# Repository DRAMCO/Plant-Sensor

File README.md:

# Plant Sensor
Documentation about the wireless plant sensing module.

# Photos

# Publications

## IEEE Sensors 2024 - Lightweight Energy-Constraint Wireless Sensor Solution for Plant Monitoring

### How to cite
```latex
@INPROCEEDINGS{10784661,
  author={Goossens, Sarah and Cappelle, Jona and Leenders, Guus and Reher, Thomas and De Smedt, Valentijn and Van de Poel, Bram and De Strycker, Lieven and Van der Perre, Liesbet},
  booktitle={2024 IEEE SENSORS}, 
  title={Lightweight Energy-Constraint Wireless Sensor Solution for Plant Monitoring}, 
  year={2024},
  volume={},
  number={},
  pages={1-4},
  keywords={Wireless communication;Smart agriculture;Wireless sensor networks;Tracking;Crops;Real-time systems;Sensors;Biomedical monitoring;Monitoring;Stress;Smart farming;horticulture;motion detection;IMU;LoRa;Internet of Things},
  doi={10.1109/SENSORS60989.2024.10784661}}
```

## IEEE Sensors Journal - Plant-wearable Wireless Sensing Solution for Autonomous Monitoring

### How to cite
```latex
@ARTICLE{11351320,
  author={Goossens, Sarah and Cappelle, Jona and Leenders, Guus and Reher, Thomas and Smedt, Valentijn De and Poel, Bram Van De and Strycker, Lieven De and Perre, Liesbet Van Der},
  journal={IEEE Sensors Journal}, 
  title={Plant-wearable Wireless Sensing Solution for Autonomous Monitoring}, 
  year={2026},
  volume={},
  number={},
  pages={1-1},
  keywords={Sensors;Crops;Wireless communication;Monitoring;Biomedical monitoring;Wireless sensor networks;Intelligent sensors;Green products;Batteries;Stress;Inertial Measurement Unit (IMU);plant monitoring;Horticultural sensor;plant-wearable;early stress detection;wireless connectivity},
  doi={10.1109/JSEN.2026.3651894}}
```

## IEEE Sensors 2025 - RF-Powered Batteryless Plant Movement Sensor for Precision Agriculture

### How to cite
```latex
@INPROCEEDINGS{11330430,
  author={Cappelle, Jona and Van Mulders, Jarne and Goossens, Sarah and Reher, Thomas and Van der Perre, Liesbet and De Strycker, Lieven and Van de Poel, Bram and Callebaut, Gilles},
  booktitle={2025 IEEE SENSORS}, 
  title={RF-Powered Batteryless Plant Movement Sensor for Precision Agriculture}, 
  year={2025},
  volume={},
  number={},
  pages={1-4},
  keywords={Radio frequency;Precision agriculture;Smart agriculture;Measurement units;Plants (biology);Maintenance;Synchronization;Internet of Things;Monitoring;Stress;Smart agriculture;Energy harvesting;Internet of Things},
  doi={10.1109/SENSORS59705.2025.11330430}}

```

## EUCNC 2025 - Attributional Life-cycle Assessment of Wireless Plant Sensing Module
[Detailed description of the LCA](LCA/Detailed_impact.md)

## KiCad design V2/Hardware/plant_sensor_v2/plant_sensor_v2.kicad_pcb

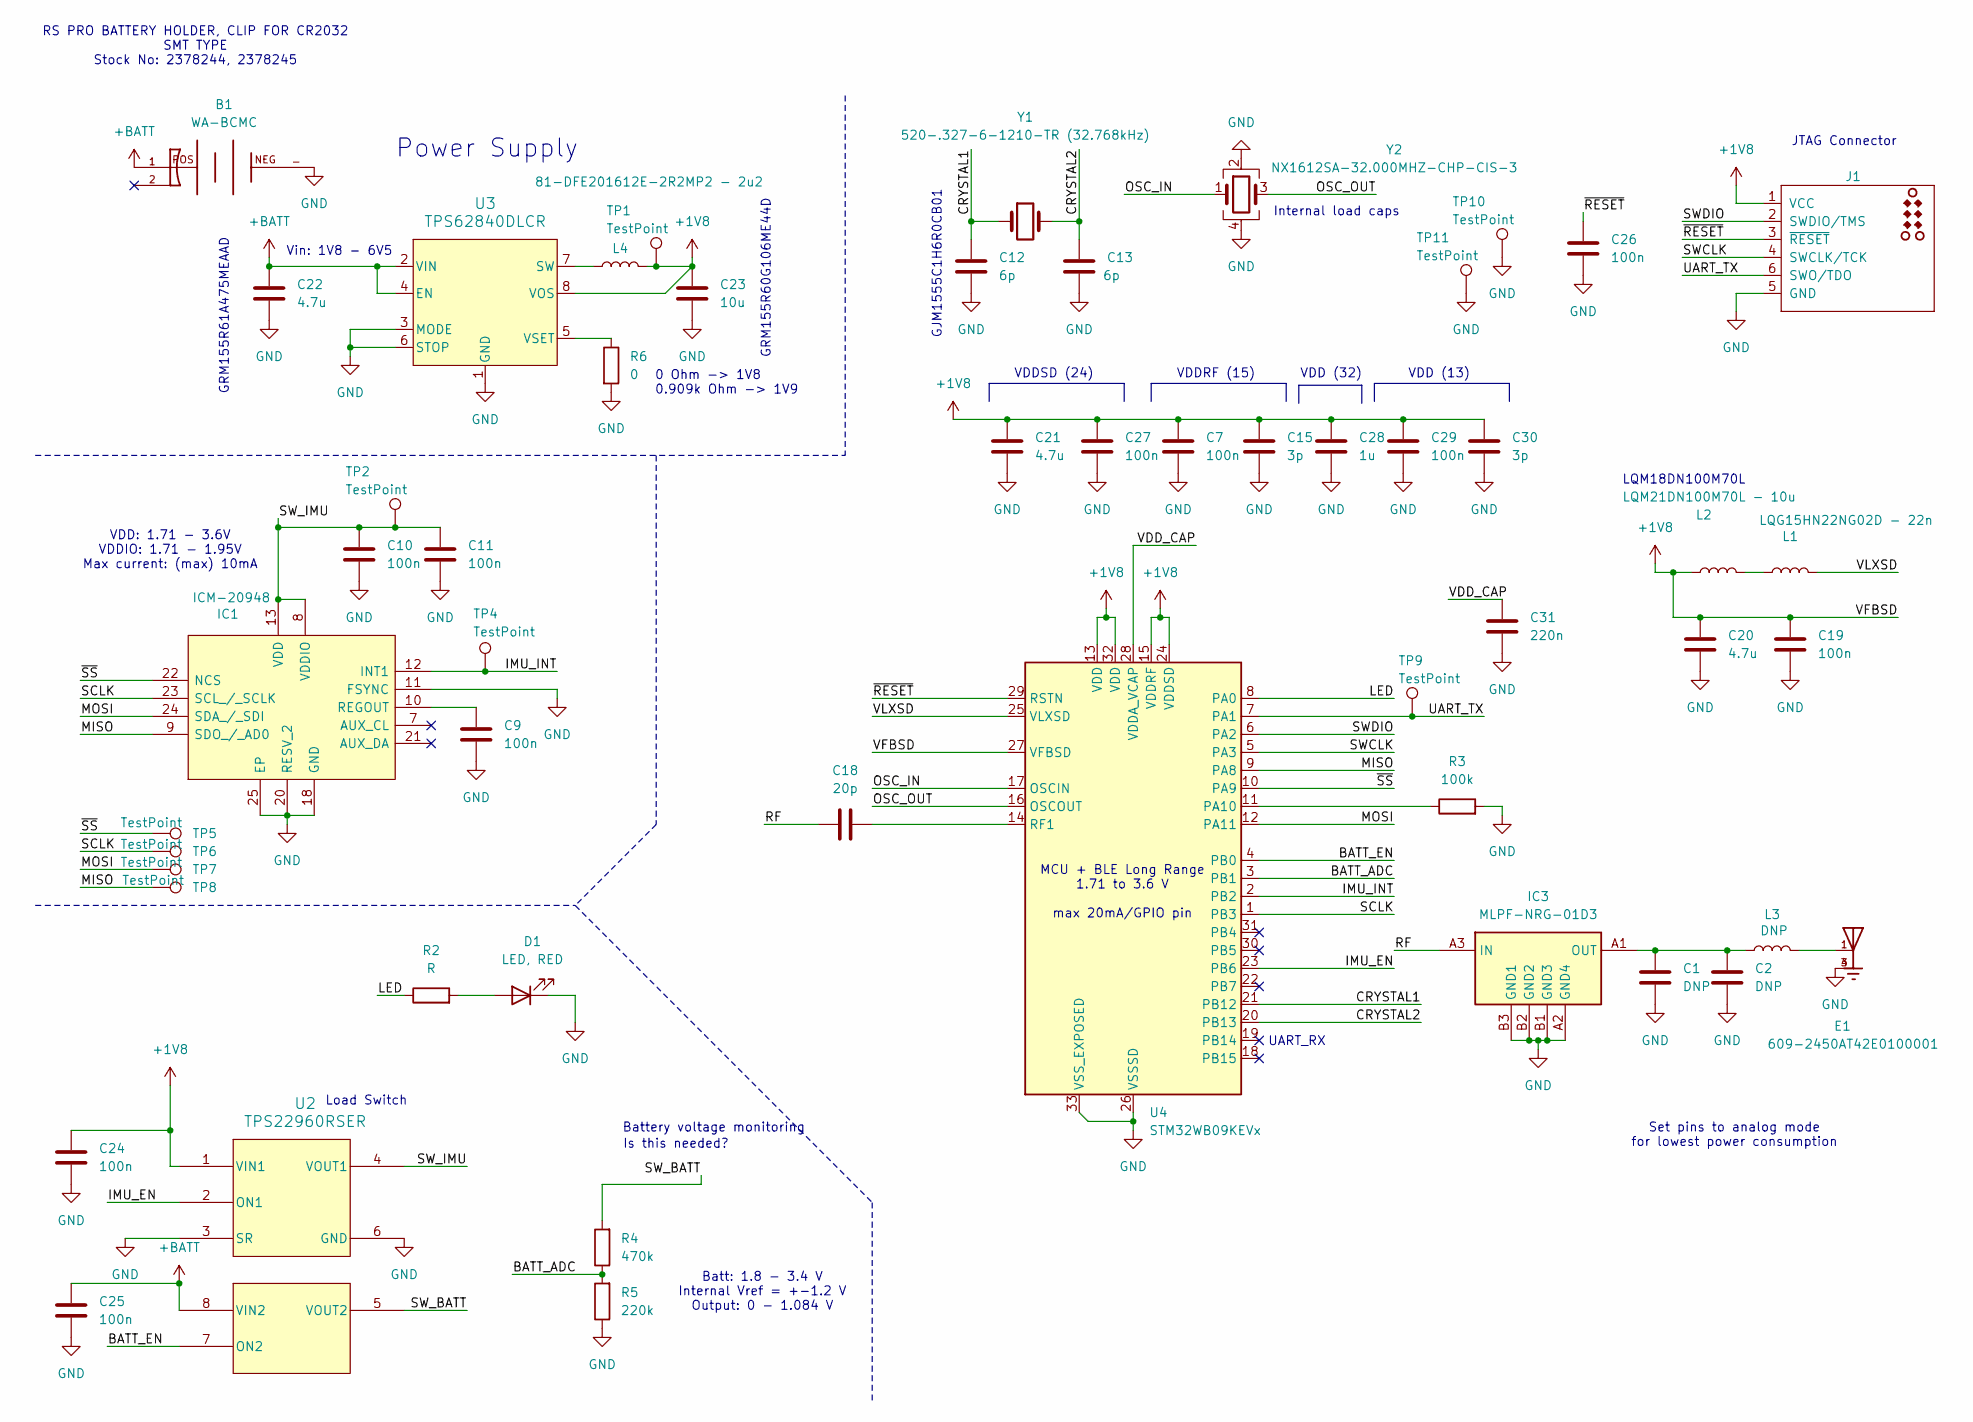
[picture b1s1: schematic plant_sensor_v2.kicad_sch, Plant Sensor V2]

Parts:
B1: WA-BCMC; WA-BCMC_79523211; PART-NUMBER 79523141
C1, C2: DNP; C_0402_1005Metric
C7, C9, C10, C11, C19, C24, C25, C26, C27, C29: 100n; C_0402_1005Metric
C12, C13: 6p; C_0402_1005Metric
C15, C30: 3p; C_0201_0603Metric
C18: 20p; C_0402_1005Metric
C20, C21, C22: 4.7u; C_0402_1005Metric
C23: 10u; C_0402_1005Metric
C28: 1u; C_0402_1005Metric
C31: 220n; C_0402_1005Metric
D1: LED, RED; LED_0603_1608Metric
E1: 609-2450AT42E0100001; XDCR_2450AT42E0100E; PARTREV 1.3
IC1: ICM-20948; ICM20948; Mouser Part Number 410-ICM-20948
IC3: MLPF-NRG-01D3; MLPFNRG01D3; Mouser Part Number 511-MLPF-NRG-01D3
J1: TC2030_SWD-MCP-NL; Tag-Connect_TC2030-IDC-NL_2x03_P1.27mm_Vertical
L1: LQG15HN22NG02D - 22n; L_0402_1005Metric
L2: LQM21DN100M70L - 10u; L_0805_2012Metric
L3: DNP; L_0402_1005Metric
L4: 81-DFE201612E-2R2MP2 - 2u2; L_Murata_DFE201610P
R2: R; R_0402_1005Metric
R3: 100k; R_0402_1005Metric
R4: 470k; R_0402_1005Metric
R5: 220k; R_0402_1005Metric
R6: 0; R_0402_1005Metric
TP1, TP2, TP4, TP5, TP6, TP7, TP8, TP9, TP10, TP11: TestPoint; TestPoint_Pad_D1.0mm
U2: TPS22960RSER; RSE0008A
U3: TPS62840DLCR; VSON8_2P1X1P6_TEX
U4: STM32WB09KEVx; QFN-32-1EP_5x5mm_P0.5mm_EP3.7x3.7mm
Y1: 520-.327-6-1210-TR (32.768kHz); XTAL_ECS-.327-6-1210-TR
Y2: NX1612SA-32.000MHZ-CHP-CIS-3; OSCSC105P160X120X35-4N

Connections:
+1V8: C7.1, C15.1, C19.1, C20.1, C21.1, C23.1, C24.1, C27.1, C28.1, C29.1, C30.1, J1.1 (VCC), L2.1, L4.2, TP1.1, U2.1 (VIN1), U3.8 (VOS), U4.13 (VDD), U4.15 (VDDRF), U4.24 (VDDSD), U4.27 (VFBSD), U4.32 (VDD)
+BATT: B1.1, C22.1, C25.1, U2.8 (VIN2), U3.2 (VIN), U3.4 (EN)
/BATT_ADC: R4.1, R5.2, U4.3 (PB1)
/BATT_EN: U2.7 (ON2), U4.4 (PB0)
/CRYSTAL1: C12.1, U4.21 (PB12), Y1.1
/CRYSTAL2: C13.1, U4.20 (PB13), Y1.2
/IMU_EN: U2.2 (ON1), U4.23 (PB6)
/IMU_INT: IC1.12 (INT1), TP4.1, U4.2 (PB2)
/LED: R2.1, U4.8 (PA0)
/MISO: IC1.9 (SDO_/_AD0), TP8.1, U4.9 (PA8)
/MOSI: IC1.24 (SDA_/_SDI), TP7.1, U4.12 (PA11)
/OSC_IN: U4.17 (OSCIN), Y2.1
/OSC_OUT: U4.16 (OSCOUT), Y2.3
/RF: C18.1, IC3.A3 (IN)
/SCLK: IC1.23 (SCL_/_SCLK), TP6.1, U4.1 (PB3)
/SWCLK: J1.4 (SWCLK/TCK), U4.5 (PA3)
/SWDIO: J1.2 (SWDIO/TMS), U4.6 (PA2)
/SW_BATT: R4.2, U2.5 (VOUT2)
/SW_IMU: C10.1, C11.1, IC1.8 (VDDIO), IC1.13 (VDD), TP2.1, U2.4 (VOUT1)
/UART_TX: J1.6 (SWO/TDO), TP9.1, U4.7 (PA1)
/VDD_CAP: C31.1, U4.28 (VDDA_VCAP)
/VLXSD: L1.2, U4.25 (VLXSD)
/~RESET: C26.2, J1.3 (~RESET), U4.29 (RSTN)
/~SS: IC1.22 (NCS), TP5.1, U4.10 (PA9)
GND: B1.-, C1.2, C2.2, C7.2, C9.2, C10.2, C11.2, C12.2, C13.2, C15.2, C19.2, C20.2, C21.2, C22.2, C23.2, C24.2, C25.2, C26.1, C27.2, C28.2, C29.2, C30.2, C31.2, D1.1 (K), E1.3, E1.4, IC1.11 (FSYNC), IC1.18 (GND), IC1.20 (RESV_2), IC1.25 (EP), IC3.A2 (GND4), IC3.B1 (GND3), IC3.B2 (GND2), IC3.B3 (GND1), J1.5 (GND), R3.2, R5.1, R6.2, TP10.1, TP11.1, U2.3 (SR), U2.6 (GND), U3.1 (GND), U3.3 (MODE), U3.6 (STOP), U4.26 (VSSSD), U4.33 (VSS_EXPOSED), Y2.2, Y2.4
unnamed: D1.2 (A), R2.2
unnamed: E1.1, L3.2
unnamed: C9.1, IC1.10 (REGOUT)
unnamed: C1.1, C2.1, IC3.A1 (OUT), L3.1
unnamed: L1.1, L2.2
unnamed: L4.1, U3.7 (SW)
unnamed: R6.1, U3.5 (VSET)
unnamed: R3.1, U4.11 (PA10)
unnamed: C18.2, U4.14 (RF1)

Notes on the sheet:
UART_RX
MCU + BLE Long Range 1.71 to 3.6 V max 20mA/GPIO pin
Vin: 1V8 - 6V5
Internal load caps
GRM155R60G106ME44D
Power Supply
RS PRO BATTERY HOLDER, CLIP FOR CR2032 SMT TYPE Stock No: 2378244, 2378245
GRM155R61A475MEAAD
VDD (32)
Battery voltage monitoring
JTAG Connector
Load Switch
Is this needed?
LQM18DN100M70L
Set pins to analog mode for lowest power consumption
VDD: 1.71 - 3.6V VDDIO: 1.71 - 1.95V Max current: (max) 10mA
VDD (13)
Batt: 1.8 - 3.4 V Internal Vref = +-1.2 V Output: 0 - 1.084 V
0 Ohm -> 1V8 0.909k Ohm -> 1V9
VDDSD (24)
VDDRF (15)
GJM1555C1H6R0CB01

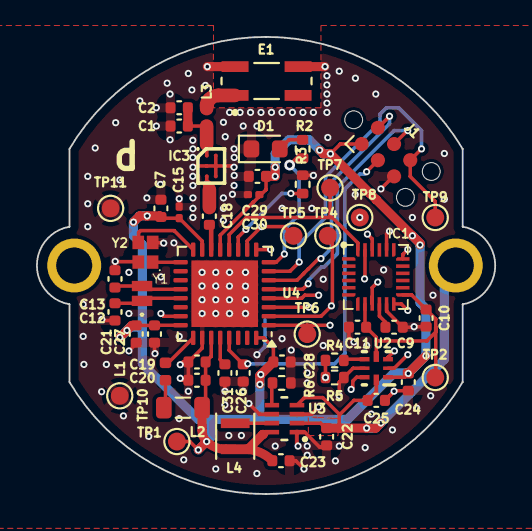
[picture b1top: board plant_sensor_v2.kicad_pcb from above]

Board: 4 copper layers, 25.5 x 25.4 mm, 53 parts (1 on the bottom side), 34 nets.

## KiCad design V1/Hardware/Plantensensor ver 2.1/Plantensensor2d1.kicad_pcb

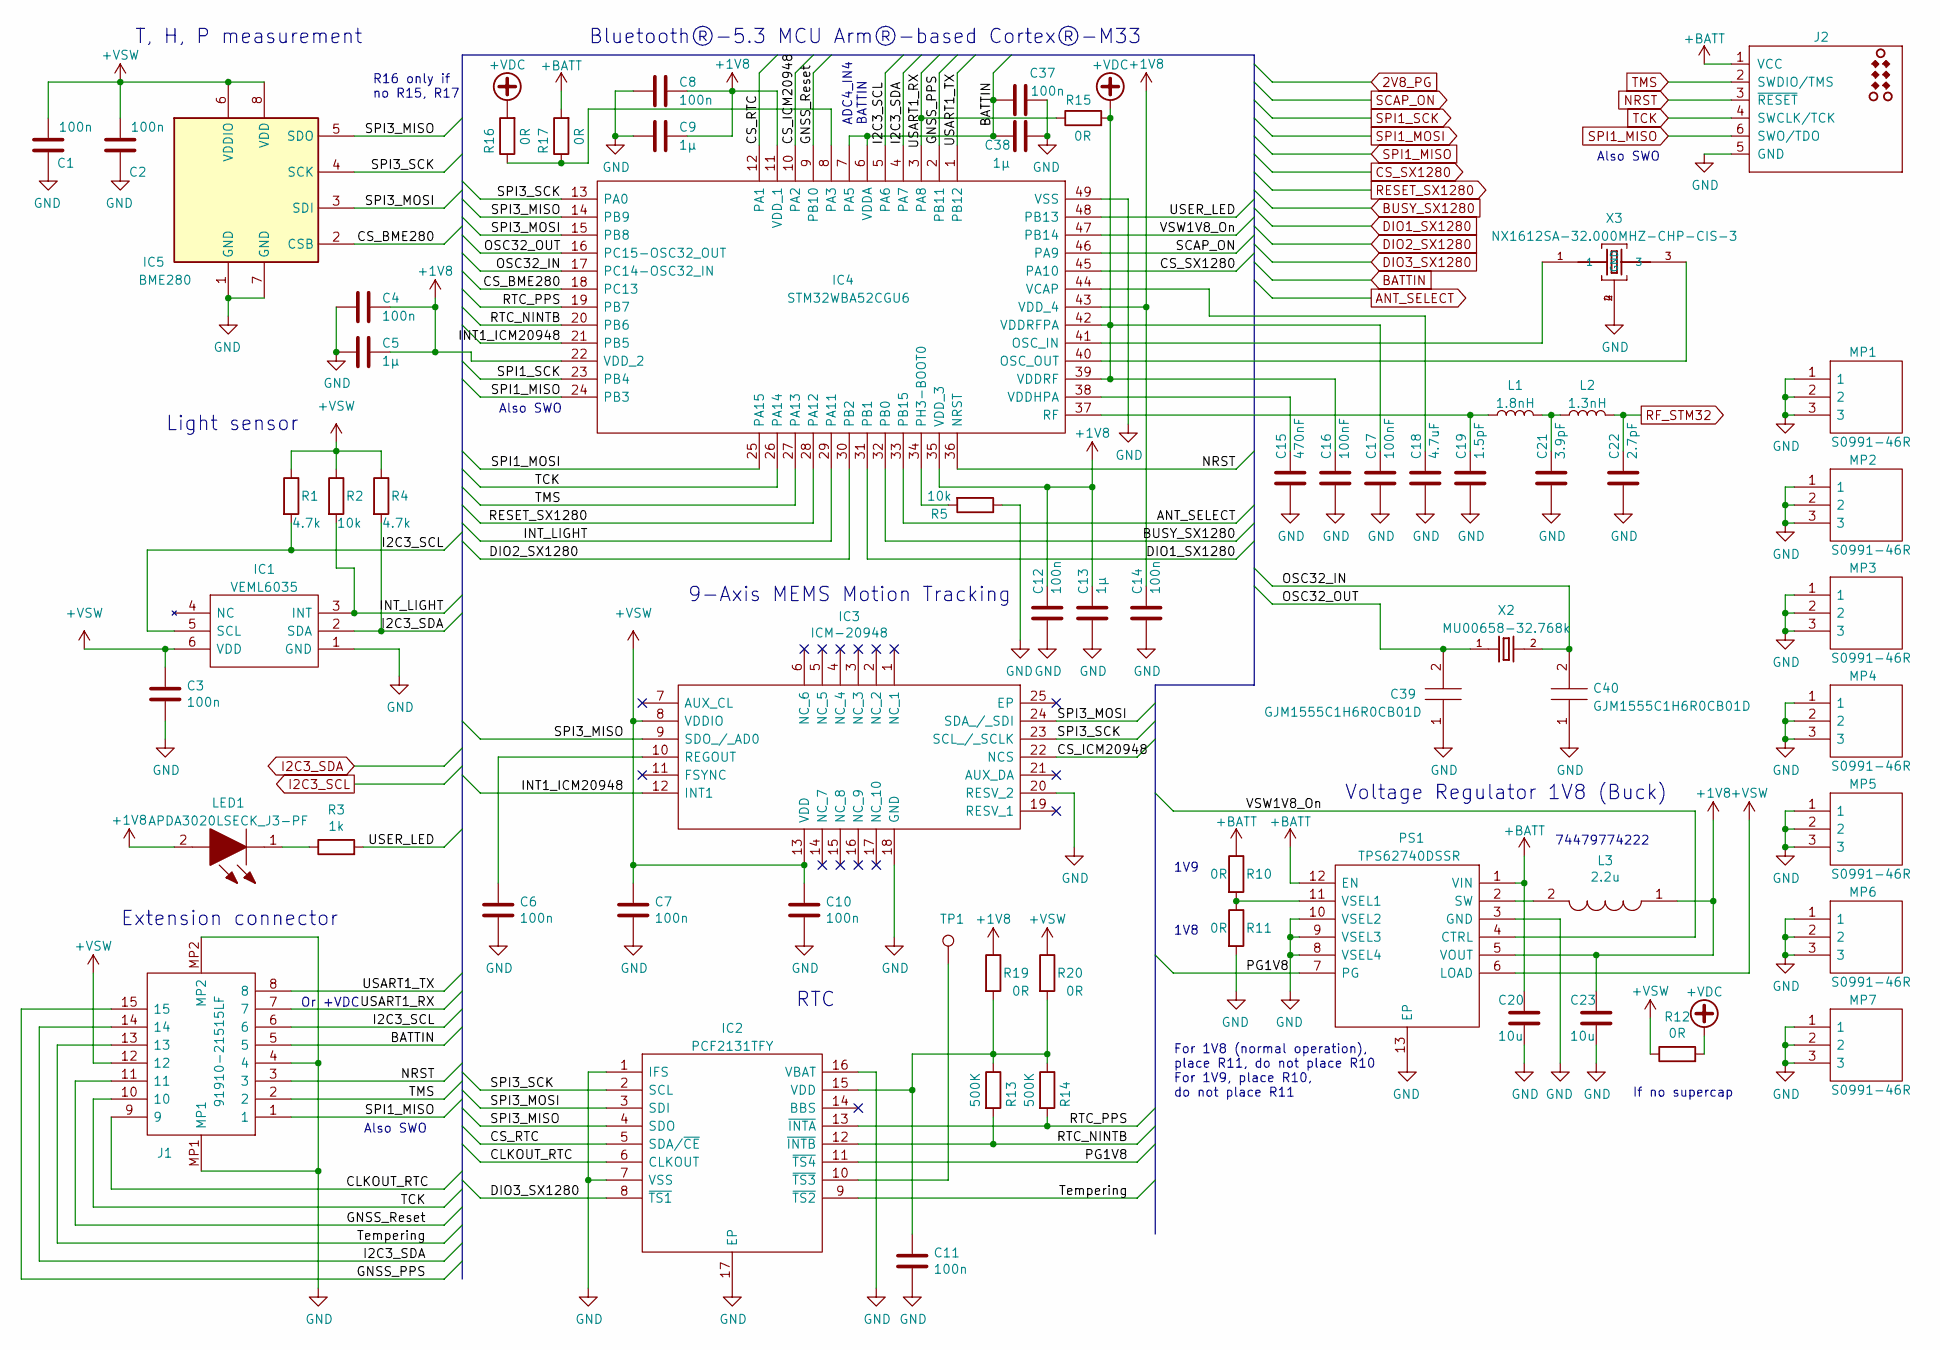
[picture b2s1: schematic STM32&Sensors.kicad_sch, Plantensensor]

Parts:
C1, C2, C3, C4, C6, C7, C8, C10, C11, C12, C14, C37: 100n; C_0402_1005Metric
C5, C9, C13, C38: 1µ; C_0603_1608Metric
C15: 470nF; C_0603_1608Metric
C16, C17: 100nF; C_0402_1005Metric
C18: 4.7uF; C_0805_2012Metric
C19: 1.5pF; C_0402_1005Metric
C20, C23: 10u; C_0805_2012Metric
C21: 3.9pF; C_0402_1005Metric
C22: 2.7pF; C_0402_1005Metric
C39, C40: GJM1555C1H6R0CB01D; CAPC1005X55N; Mouser Part Number 81-GJM1555C1H6R0CB01
IC1: VEML6035; Mouser Part Number 78-VEML6035
IC2: PCF2131TFY; SON50P350X450X150-17N-D_PCF2131TFY; Mouser Part Number 771-PCF2131TFY
IC3: ICM-20948; QFN40P300X300X105-25N-D_ICM20948; Mouser Part Number 410-ICM-20948
IC4: STM32WBA52CGU6; QFN50P700X700X65-49N-D; Mouser Part Number 511-STM32WBA52CGU6
IC5: BME280; Bosch_LGA-8_2.5x2.5mm_P0.65mm_ClockwisePinNumbering
J1: 91910-21515LF; 9191021515LF; Mouser Part Number 649-91910-21515LF
J2: TC2030_SWD-MCP-NL; TC2030-MCP-NL
L1: 1.8nH; C_0402_1005Metric
L2: 1.3nH; C_0402_1005Metric
L3: 2.2u; L_0805_2012Metric; Mouser Part Number 710-74479774222
LED1: APDA3020LSECK_J3-PF; APDA3020LSECKJ3PF; Mouser Part Number 604-APDA3020LSECKJ3F
MP1, MP2, MP3, MP4, MP5, MP6, MP7: S0991-46R; S099146R; Mouser Part Number 855-S0991-46R
PS1: TPS62740DSSR; SON50P200X300X80-13N_TPS62740DSSR; Mouser Part Number 595-TPS62740DSSR
R1, R4: 4.7k; R_0402_1005Metric
R2, R5: 10k; R_0402_1005Metric
R3: 1k; R_0603_1608Metric
R10, R11, R15, R16, R17, R19, R20: 0R; R_0402_1005Metric
R12: 0R; R_0603_1608Metric
R13, R14: 500K; R_0402_1005Metric
TP1: TestPoint; TestPoint_Pad_D1.0mm
X2: MU00658-32.768k; XTAL_ECS-.327-12.5-16-TR; DigiKey_Part_Number XC2131TR-ND
X3: NX1612SA-32.000MHZ-CHP-CIS-3; OSCSC105P160X120X35-4N

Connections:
+1V8: C4.1, C5.1, C8.1, C9.1, C12.1, C13.1, C14.1, C23.1, IC4.11 (VDD_1), IC4.22 (VDD_2), IC4.35 (VDD_3), IC4.43 (VDD_4), L3.1, LED1.2, PS1.5 (VOUT), R19.1
+BATT: C20.1, J2.1 (VCC), PS1.1 (VIN), PS1.12 (EN), R10.1, R17.2; also elsewhere on the board
+VDC: C16.1, C17.1, IC4.39 (VDDRF), IC4.42 (VDDRFPA), R12.2, R15.2, R16.2; also elsewhere on the board
+VSW: C1.1, C2.1, C3.1, C7.1, C10.1, IC1.6 (VDD), IC3.8 (VDDIO), IC3.13 (VDD), IC5.6 (VDDIO), IC5.8 (VDD), J1.12, PS1.6 (LOAD), R1.1, R2.1, R4.1, R12.1, R20.1; also elsewhere on the board
/STM32&Sensors/CLKOUT_RTC: IC2.6 (CLKOUT), J1.9
/STM32&Sensors/CS_BME280: IC4.18 (PC13), IC5.2 (CSB)
/STM32&Sensors/CS_ICM20948: IC3.22 (NCS), IC4.10 (PA2)
/STM32&Sensors/CS_RTC: IC2.5 (SDA/~CE), IC4.12 (PA1)
/STM32&Sensors/GNSS_PPS: IC4.2 (PB11), J1.15
/STM32&Sensors/GNSS_Reset: IC4.9 (PB10), J1.11
/STM32&Sensors/INT1_ICM20948: IC3.12 (INT1), IC4.21 (PB5)
/STM32&Sensors/INT_LIGHT: IC1.3 (INT), IC4.29 (PA11), R2.2
/STM32&Sensors/OSC32_IN: C40.2, IC4.17 (PC14-OSC32_IN), X2.2
/STM32&Sensors/OSC32_OUT: C39.2, IC4.16 (PC15-OSC32_OUT), X2.1
/STM32&Sensors/PG1V8: IC2.11 (~TS4), PS1.7 (PG)
/STM32&Sensors/RTC_NINTB: IC2.12 (~INTB), IC4.20 (PB6), R13.2
/STM32&Sensors/RTC_PPS: IC2.13 (~INTA), IC4.19 (PB7), R14.2
/STM32&Sensors/SPI3_MISO: IC2.4 (SDO), IC3.9 (SDO_/_AD0), IC4.14 (PB9), IC5.5 (SDO)
/STM32&Sensors/SPI3_MOSI: IC2.3 (SDI), IC3.24 (SDA_/_SDI), IC4.15 (PB8), IC5.3 (SDI)
/STM32&Sensors/SPI3_SCK: IC2.2 (SCL), IC3.23 (SCL_/_SCLK), IC4.13 (PA0), IC5.4 (SCK)
/STM32&Sensors/Tempering: IC2.9 (~TS2), J1.13
/STM32&Sensors/USART1_RX: IC4.3 (PA8), J1.7, R15.1
/STM32&Sensors/USART1_TX: IC4.1 (PB12), J1.8
/STM32&Sensors/USER_LED: IC4.48 (PB13), R3.2
/STM32&Sensors/VSW1V8_On: IC4.47 (PB14), PS1.4 (CTRL)
ANT_SELECT: IC4.33 (PB15); also elsewhere on the board
BATTIN: C37.1, C38.1, IC4.6 (VDDA), IC4.7 (PA5), J1.5; also elsewhere on the board
BUSY_SX1280: IC4.32 (PB0); also elsewhere on the board
CS_SX1280: IC4.45 (PA10); also elsewhere on the board
DIO1_SX1280: IC4.31 (PB1); also elsewhere on the board
DIO2_SX1280: IC4.30 (PB2); also elsewhere on the board
DIO3_SX1280: IC2.8 (~TS1); also elsewhere on the board
GND: C1.2, C2.2, C3.2, C4.2, C5.2, C6.2, C7.2, C8.2, C9.2, C10.2, C11.2, C12.2, C13.2, C14.2, C15.2, C16.2, C17.2, C18.2, C19.2, C20.2, C21.2, C22.2, C23.2, C37.2, C38.2, C39.1, C40.1, IC1.1 (GND), IC2.1 (IFS), IC2.7 (VSS), IC2.16 (VBAT), IC2.17 (EP), IC3.18 (GND), IC3.20 (RESV_2), IC4.49 (VSS), IC5.1 (GND), IC5.7 (GND), J1.4, J1.MP1, J1.MP2, J2.5 (GND), MP1.1, MP1.2, MP1.3, MP2.1, MP2.2, MP2.3, MP3.1, MP3.2, MP3.3, MP4.1, MP4.2, MP4.3, MP5.1, MP5.2, MP5.3, MP6.1, MP6.2, MP6.3, MP7.1, MP7.2, MP7.3, PS1.3 (GND), PS1.8 (VSEL4), PS1.9 (VSEL3), PS1.10 (VSEL2), PS1.13 (EP), R5.1, R11.2, X3.2 (GND), X3.4 (GND); also elsewhere on the board
I2C3_SCL: IC1.5 (SCL), IC4.5 (PA6), J1.6, R1.2; also elsewhere on the board
I2C3_SDA: IC1.2 (SDA), IC4.4 (PA7), J1.14, R4.2; also elsewhere on the board
NRST: IC4.36 (NRST), J1.3, J2.3 (~RESET)
unnamed: C6.1, IC3.10 (REGOUT)
unnamed: C11.1, IC2.15 (VDD), R13.1, R14.1, R19.2, R20.2
unnamed: C15.1, IC4.38 (VDDHPA)
unnamed: C18.1, IC4.44 (VCAP)
unnamed: C19.1, IC4.37 (RF), L1.1
unnamed: C21.1, L1.2, L2.1
unnamed: IC2.10 (~TS3), TP1.1
unnamed: IC4.8 (PA3), R16.1, R17.1
unnamed: IC4.34 (PH3-BOOT0), R5.2
unnamed: IC4.40 (OSC_OUT), X3.3
unnamed: IC4.41 (OSC_IN), X3.1
unnamed: L3.2, PS1.2 (SW)
unnamed: LED1.1, R3.1
unnamed: PS1.11 (VSEL1), R10.2, R11.1
RESET_SX1280: IC4.28 (PA12); also elsewhere on the board
RF_STM32: C22.1, L2.2; also elsewhere on the board
SCAP_ON: IC4.46 (PA9); also elsewhere on the board
SPI1_MISO: IC4.24 (PB3), J1.1, J2.6 (SWO/TDO); also elsewhere on the board
SPI1_MOSI: IC4.25 (PA15); also elsewhere on the board
SPI1_SCK: IC4.23 (PB4); also elsewhere on the board
TCK: IC4.26 (PA14), J1.10, J2.4 (SWCLK/TCK)
TMS: IC4.27 (PA13), J1.2, J2.2 (SWDIO/TMS)

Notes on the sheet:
Voltage Regulator 1V8 (Buck)
R16 only if no R15, R17
9-Axis MEMS Motion Tracking
Extension connector
RTC
ADC4_IN4 BATTIN
Also SWO
Light sensor
1V8
Bluetooth®-5.3 MCU Arm®-based Cortex®-M33
74479774222
Or +VDC
For 1V8 (normal operation), place R11, do not place R10 For 1V9, place R10, do not place R11
T, H, P measurement
If no supercap
1V9

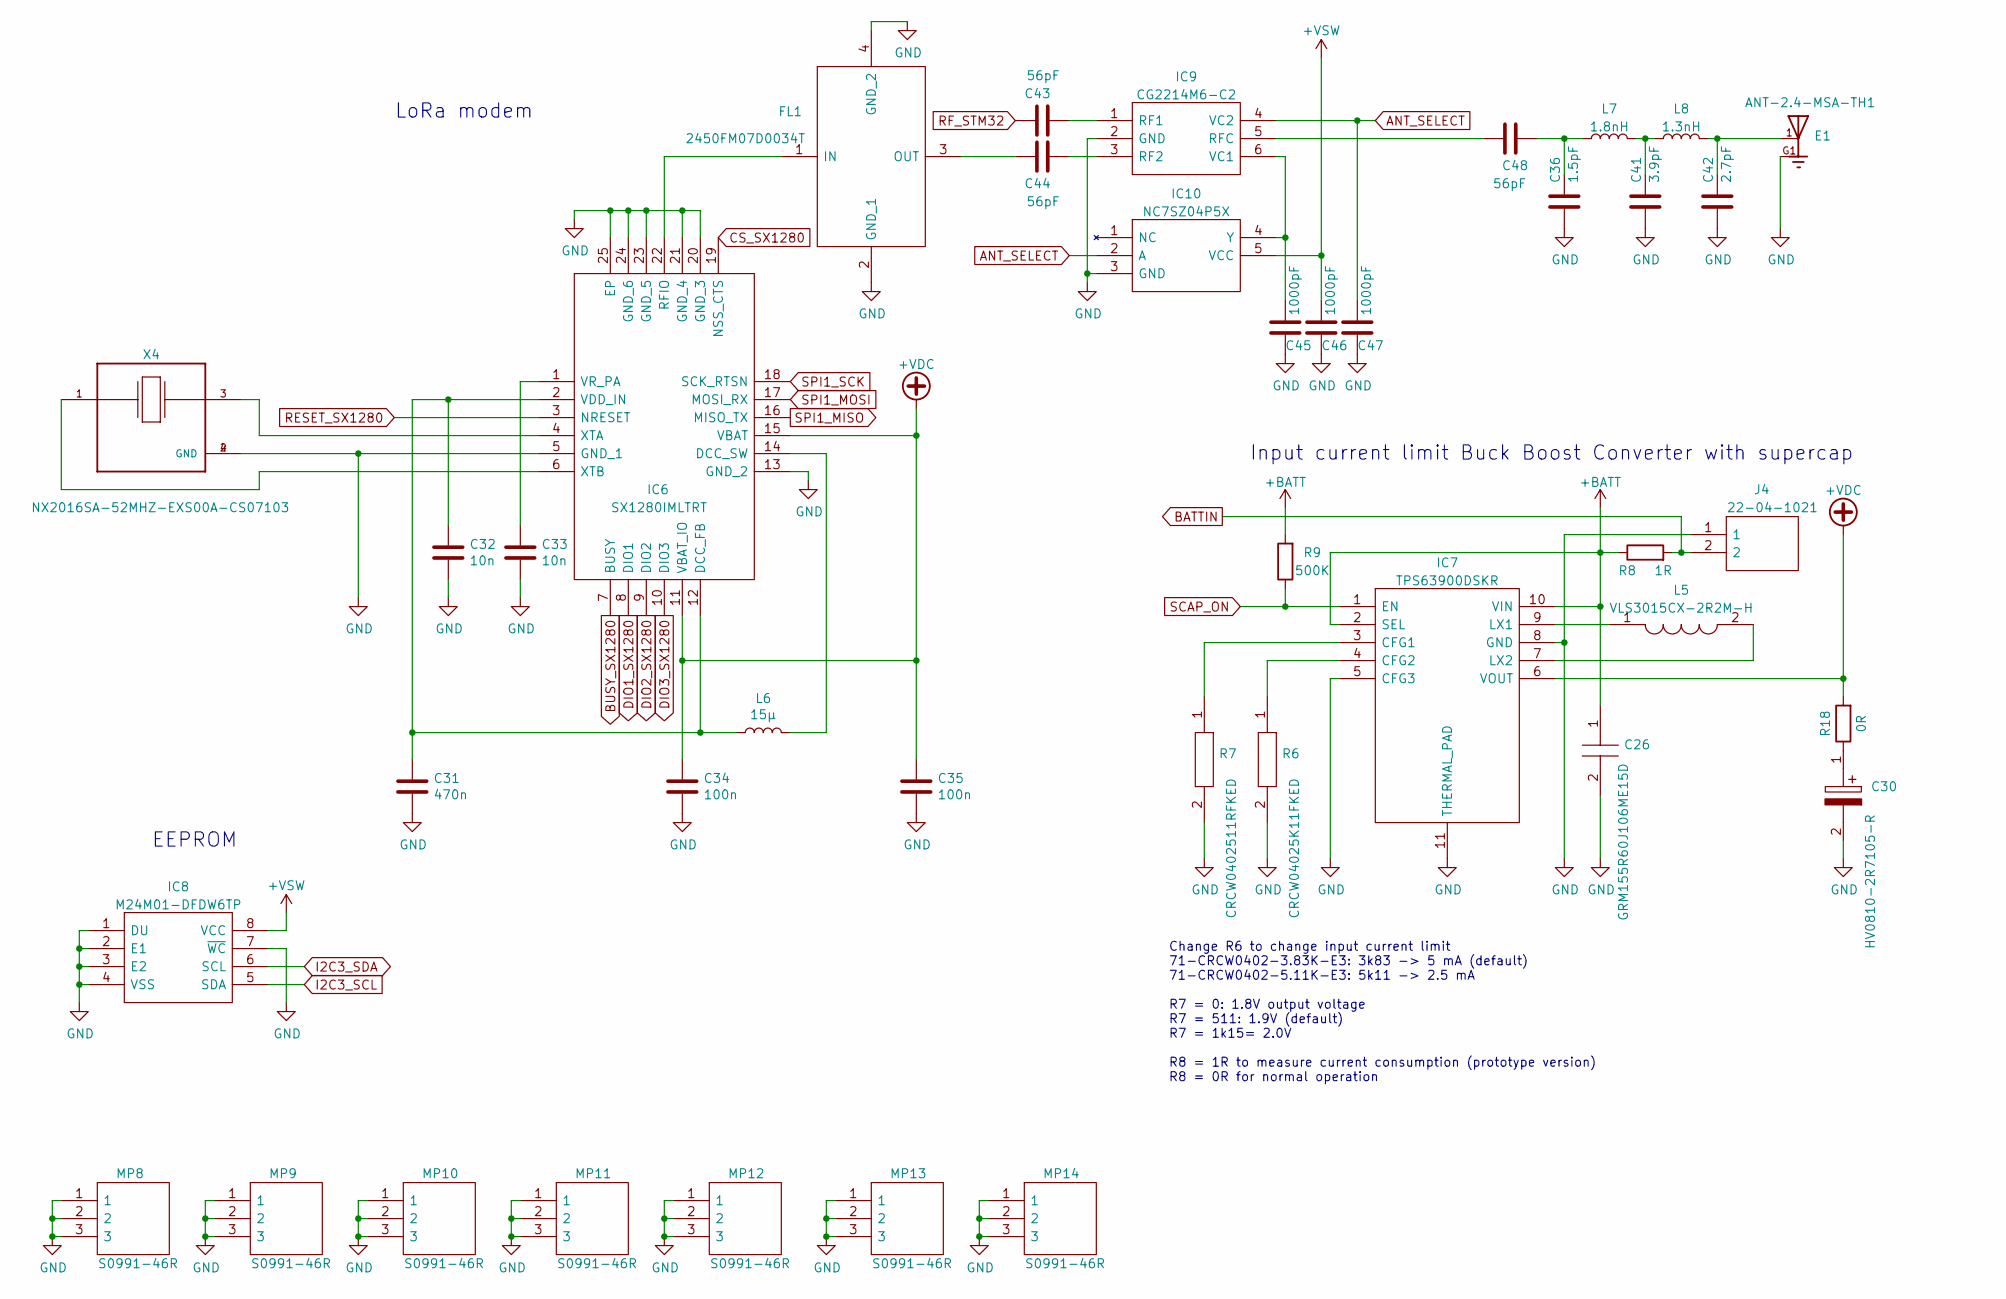
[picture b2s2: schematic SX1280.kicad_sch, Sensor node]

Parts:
C26: GRM155R60J106ME15D; CAPC1005X55N; Mouser Part Number 81-GRM155R60J106ME5D
C30: HV0810-2R7105-R; CAPPRD350W52D800H1350; Mouser Part Number 504-HV0810-2R7105-R
C31: 470n; C_0603_1608Metric
C32, C33: 10n; C_0603_1608Metric
C34, C35: 100n; C_0402_1005Metric
C36: 1.5pF; C_0402_1005Metric
C41: 3.9pF; C_0402_1005Metric
C42: 2.7pF; C_0402_1005Metric
C43, C44, C48: 56pF; C_0402_1005Metric
C45, C46, C47: 1000pF; C_0402_1005Metric
E1: ANT-2.4-MSA-TH1; XCVR_ANT-2.4-MSA-TH1; PARTREV A; DigiKey_Part_Number 343-ANT-2.4-MSA-TH1-ND
FL1: 2450FM07D0034T; Mouser Part Number 609-2450FM07D0034T
IC6: SX1280IMLTRT; QFN50P400X400X100-25N-D_SX1280; Mouser Part Number 947-SX1280IMLTRT
IC7: TPS63900DSKR; SON50P250X250X80-11N-D; Mouser Part Number 595-TPS63900DSKR
IC8: M24M01-DFDW6TP; SOP65P640X120-8N; Mouser Part Number 511-M24M01-DFDW6TP
IC9: CG2214M6-C2; SOTFL48P130X55-6N; Mouser Part Number 551-CG2214M6-C2
IC10: NC7SZ04P5X; SOT65P210X110-5N; Mouser Part Number 512-NC7SZ04P5X
J4: 22-04-1021; SHDR2W64P0X250_1X2_450X580X1170P; Mouser Part Number 538-22-04-1021
L5: VLS3015CX-2R2M-H; VLS3015; Mouser Part Number 810-VLS3015CX-2R2M-H
L6: 15µ; L_0603_1608Metric
L7: 1.8nH; C_0402_1005Metric
L8: 1.3nH; C_0402_1005Metric
MP8, MP9, MP10, MP11, MP12, MP13, MP14: S0991-46R; S099146R; Mouser Part Number 855-S0991-46R
R6: CRCW04025K11FKED; RESC1005X40N; Mouser Part Number 71-CRCW0402-5.11K-E3
R7: CRCW0402511RFKED; RESC1005X40N; Mouser Part Number 71-CRCW0402-511-E3
R8: 1R; R_0805_2012Metric
R9: 500K; R_0402_1005Metric
R18: 0R; R_0603_1608Metric
X4: NX2016SA-52MHZ-EXS00A-CS07103; OSCCC200X160X50N; PARTREV N/A

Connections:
+BATT: C26.1, IC7.2 (SEL), IC7.10 (VIN), R8.1, R9.2; also elsewhere on the board
+VDC: C34.1, C35.1, IC6.11 (VBAT_IO), IC6.15 (VBAT), IC7.6 (VOUT), R18.2; also elsewhere on the board
+VSW: C46.2, IC8.8 (VCC), IC10.5 (VCC); also elsewhere on the board
ANT_SELECT: C47.2, IC9.4 (VC2), IC10.2 (A); also elsewhere on the board
BATTIN: J4.2, R8.2; also elsewhere on the board
BUSY_SX1280: IC6.7 (BUSY); also elsewhere on the board
CS_SX1280: IC6.19 (NSS_CTS); also elsewhere on the board
DIO1_SX1280: IC6.8 (DIO1); also elsewhere on the board
DIO2_SX1280: IC6.9 (DIO2); also elsewhere on the board
DIO3_SX1280: IC6.10 (DIO3); also elsewhere on the board
GND: C26.2, C30.2, C31.2, C32.2, C33.2, C34.2, C35.2, C36.2, C41.2, C42.2, C45.1, C46.1, C47.1, E1.G1, FL1.2 (GND_1), FL1.4 (GND_2), IC6.5 (GND_1), IC6.13 (GND_2), IC6.20 (GND_3), IC6.21 (GND_4), IC6.23 (GND_5), IC6.24 (GND_6), IC6.25 (EP), IC7.5 (CFG3), IC7.8 (GND), IC7.11 (THERMAL_PAD), IC8.1 (DU), IC8.2 (E1), IC8.3 (E2), IC8.4 (VSS), IC8.7 (~WC), IC9.2 (GND), IC10.3 (GND), J4.1, MP8.1, MP8.2, MP8.3, MP9.1, MP9.2, MP9.3, MP10.1, MP10.2, MP10.3, MP11.1, MP11.2, MP11.3, MP12.1, MP12.2, MP12.3, MP13.1, MP13.2, MP13.3, MP14.1, MP14.2, MP14.3, R6.2, R7.2, X4.2 (GND), X4.4 (GND); also elsewhere on the board
I2C3_SCL: IC8.5 (SDA); also elsewhere on the board
I2C3_SDA: IC8.6 (SCL); also elsewhere on the board
unnamed: C30.1, R18.1
unnamed: C31.1, C32.1, IC6.2 (VDD_IN), IC6.12 (DCC_FB), L6.1
unnamed: C33.1, IC6.1 (VR_PA)
unnamed: C36.1, C48.1, L7.1
unnamed: C41.1, L7.2, L8.1
unnamed: C42.1, E1.1, L8.2
unnamed: C43.2, IC9.1 (RF1)
unnamed: C44.1, FL1.3 (OUT)
unnamed: C44.2, IC9.3 (RF2)
unnamed: C45.2, IC9.6 (VC1), IC10.4 (Y)
unnamed: C48.2, IC9.5 (RFC)
unnamed: FL1.1 (IN), IC6.22 (RFIO)
unnamed: IC6.4 (XTA), X4.3
unnamed: IC6.6 (XTB), X4.1
unnamed: IC6.14 (DCC_SW), L6.2
unnamed: IC7.3 (CFG1), R7.1
unnamed: IC7.4 (CFG2), R6.1
unnamed: IC7.7 (LX2), L5.2
unnamed: IC7.9 (LX1), L5.1
RESET_SX1280: IC6.3 (NRESET); also elsewhere on the board
RF_STM32: C43.1; also elsewhere on the board
SCAP_ON: IC7.1 (EN), R9.1; also elsewhere on the board
SPI1_MISO: IC6.16 (MISO_TX); also elsewhere on the board
SPI1_MOSI: IC6.17 (MOSI_RX); also elsewhere on the board
SPI1_SCK: IC6.18 (SCK_RTSN); also elsewhere on the board

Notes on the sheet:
LoRa modem
Input current limit Buck Boost Converter with supercap
EEPROM
Change R6 to change input current limit 71-CRCW0402-3.83K-E3: 3k83 -> 5 mA (default) 71-CRCW0402-5.11K-E3: 5k11 -> 2.5 mA R7 = 0: 1.8V output voltage R7 = 511: 1.9V (default) R7 = 1k15= 2.0V R8 = 1R to measure current consumption (prototype version) R8 = 0R for normal operation

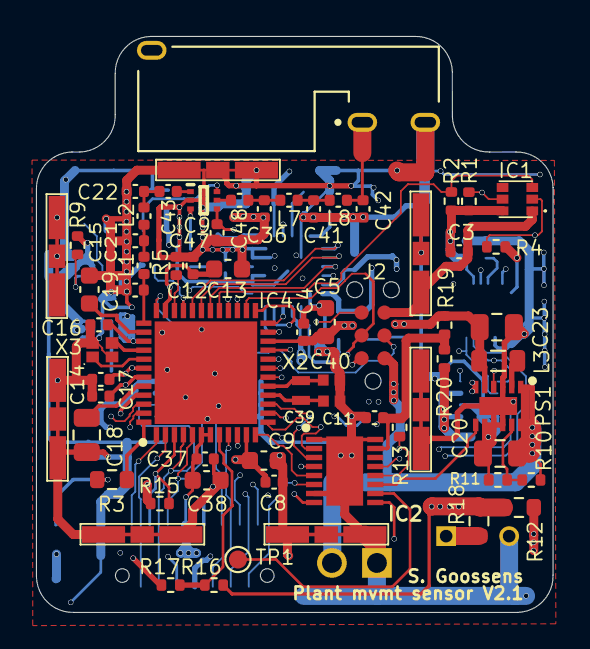
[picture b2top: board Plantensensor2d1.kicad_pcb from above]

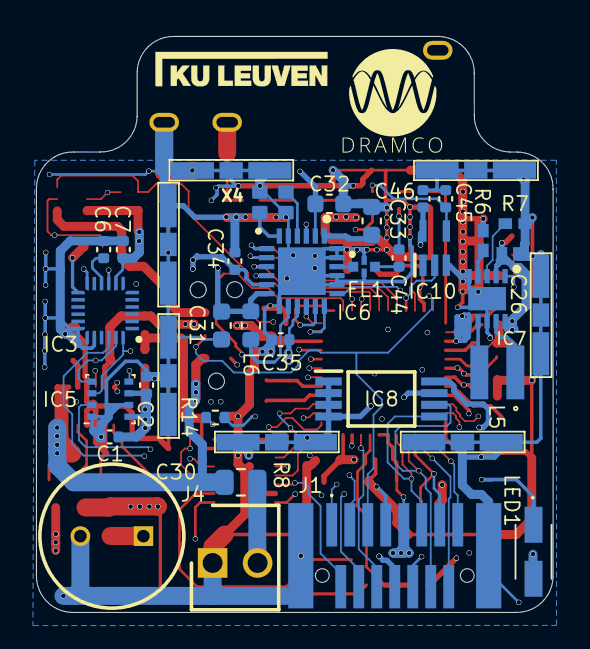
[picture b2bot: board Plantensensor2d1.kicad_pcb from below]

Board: 4 copper layers, 28.7 x 32.0 mm, 104 parts (38 on the bottom side), 77 nets.

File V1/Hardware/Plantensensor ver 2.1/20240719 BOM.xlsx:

Id | Designator | Package | Quantity | Designation | Supplier and ref | Column1
1 | R16,R15,R20,R11,R10,R17,R19 | R_0402_1005Metric | 7 | 0R
2 | C37,C11,C14,C12,C4,C8,C3,C2,C7,C35,C6,C34,C1 | C_0402_1005Metric | 13 | 100n
3 | R2,R5 | R_0402_1005Metric | 2 | 10k
4 | PS1 | SON50P200X300X80-13N_TPS62740DSSR | 1 | TPS62740DSSR
5 | IC4 | QFN50P700X700X65-49N-D | 1 | STM32WBA52CGU6
6 | C19,C36 | C_0402_1005Metric | 2 | 1.5pF
7 | C18 | C_0805_2012Metric | 1 | 4.7uF
8 | R1,R4 | R_0402_1005Metric | 2 | 4.7k
9 | R18,R12 | R_0603_1608Metric | 2 | 0R
10 | C42,C22 | C_0402_1005Metric | 2 | 2.7pF
11 | C16,C17 | C_0402_1005Metric | 2 | 100nF
12 | C9,C38,C5,C13 | C_0603_1608Metric | 4 | 1µ
13 | TP1 | TestPoint_Pad_D1.0mm | 1 | TestPoint
14 | L8,L2 | C_0402_1005Metric | 2 | 1.3nH
15 | L3 | L_0805_2012Metric | 1 | 2.2u
16 | C39,C40 | CAPC1005X55N | 2 | GJM1555C1H6R0CB01D
17 | C20,C23 | C_0805_2012Metric | 2 | 10u
18 | MP2,MP7,MP4,MP5,MP3,MP1,MP6,MP11,MP8,MP12,MP9,MP14,MP10,MP13 | S099146R | 14 | S0991-46R
19 | C48,C43,C44 | C_0402_1005Metric | 3 | 56pF
20 | R9,R13,R14 | R_0402_1005Metric | 3 | 500K
21 | C41,C21 | C_0402_1005Metric | 2 | 3.9pF
22 | IC9 | SOTFL48P130X55-6N | 1 | CG2214M6-C2
23 | IC1 | VEML6035 | 1 | VEML6035
24 | C47,C46,C45 | C_0402_1005Metric | 3 | 1000pF
25 | X2 | XTAL_ECS-.327-12.5-16-TR | 1 | MU00658-32.768k
26 | L7,L1 | C_0402_1005Metric | 2 | 1.8nH
27 | E1 | XCVR_ANT-2.4-MSA-TH1 | 1 | ANT-2.4-MSA-TH1
28 | IC2 | SON50P350X450X150-17N-D_PCF2131TFY | 1 | PCF2131TFY
29 | X3 | OSCSC105P160X120X35-4N | 1 | NX1612SA-32.000MHZ-CHP-CIS-3
30 | C15 | C_0603_1608Metric | 1 | 470nF
31 | J2 | TC2030-MCP-NL | 1 | TC2030_SWD-MCP-NL
32 | R3 | R_0603_1608Metric | 1 | 1k
33 | IC8 | SOP65P640X120-8N | 1 | M24M01-DFDW6TP
34 | J4 | SHDR2W64P0X250_1X2_450X580X1170P | 1 | 22-04-1021
35 | IC5 | Bosch_LGA-8_2.5x2.5mm_P0.65mm_ClockwisePinNumbering | 1 | BME280
36 | FL1 | 2450FM07D0034T | 1 | 2450FM07D0034T
37 | C33,C32 | C_0603_1608Metric | 2 | 10n
38 | C26 | CAPC1005X55N | 1 | GRM155R60J106ME15D
39 | IC3 | QFN40P300X300X105-25N-D_ICM20948 | 1 | ICM-20948
40 | IC6 | QFN50P400X400X100-25N-D_SX1280 | 1 | SX1280IMLTRT
41 | L5 | VLS3015 | 1 | VLS3015CX-2R2M-H
42 | R6 | RESC1005X40N | 1 | CRCW04025K11FKED
43 | R8 | R_0805_2012Metric | 1 | 1R
44 | C31 | C_0603_1608Metric | 1 | 470n
45 | IC7 | SON50P250X250X80-11N-D | 1 | TPS63900DSKR
46 | IC10 | SOT65P210X110-5N | 1 | NC7SZ04P5X
47 | G*** | KULeuven6000 | 1 | LOGO
48 | X4 | OSCCC200X160X50N | 1 | NX2016SA-52MHZ-EXS00A-CS07103
49 | LED1 | APDA3020LSECKJ3PF | 1 | APDA3020LSECK_J3-PF
50 | J1 | 9191021515LF | 1 | 91910-21515LF
51 | L6 | L_0603_1608Metric | 1 | 15µ
52 | C30 | CAPPRD350W52D800H1350 | 1 | HV0810-2R7105-R
53 | R7 | RESC1005X40N | 1 | CRCW0402511RFKED

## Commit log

2025-01-15 v2 start pcb design
2025-01-15 restructuring
2025-01-15 Software v1
2025-01-15 hardware update
2025-01-16 update hardware
2025-01-24 teseting software
2025-01-24 ble example test
2025-01-30 Hardware design, almost finished
2025-01-30 cleanup software
2025-01-31 Hardware V2 Finished
2025-02-12 Software BLE beacon in STM32IDE
2025-02-12 update software
2025-02-12 custom service based on eddystone uid
2025-02-19 Software update - sequencer, LED, and Batt and IMU enable
2025-02-24 temp update
2025-02-25 Software possible to send Coded PHY packets
2025-02-25 Increase TX power
2025-02-27 SPI (not working yet)
2025-03-04 update ICM20948
2025-03-10 ICM20948 meas working via SPI
2025-03-10 enable ble
2025-03-11 Receiver with BLE advertising packets working
2025-03-11 hardware copy
2026-03-10 readme
2026-03-10 photos
2026-03-10 Add photos section to README
    Added photos section with images of the plant sensor.

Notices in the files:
parts and their libraries:
©2009 ROFA.cz - modified and updated by Robert Darlington ‹rdarlington@gmail.com›
